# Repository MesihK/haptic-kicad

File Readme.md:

## Motor Controller Device for Zenom Hardware In-the-loop Environment

This device is used for nonliner control of mechanical systems via 
actuators.

Mesih Veysi Kilinc

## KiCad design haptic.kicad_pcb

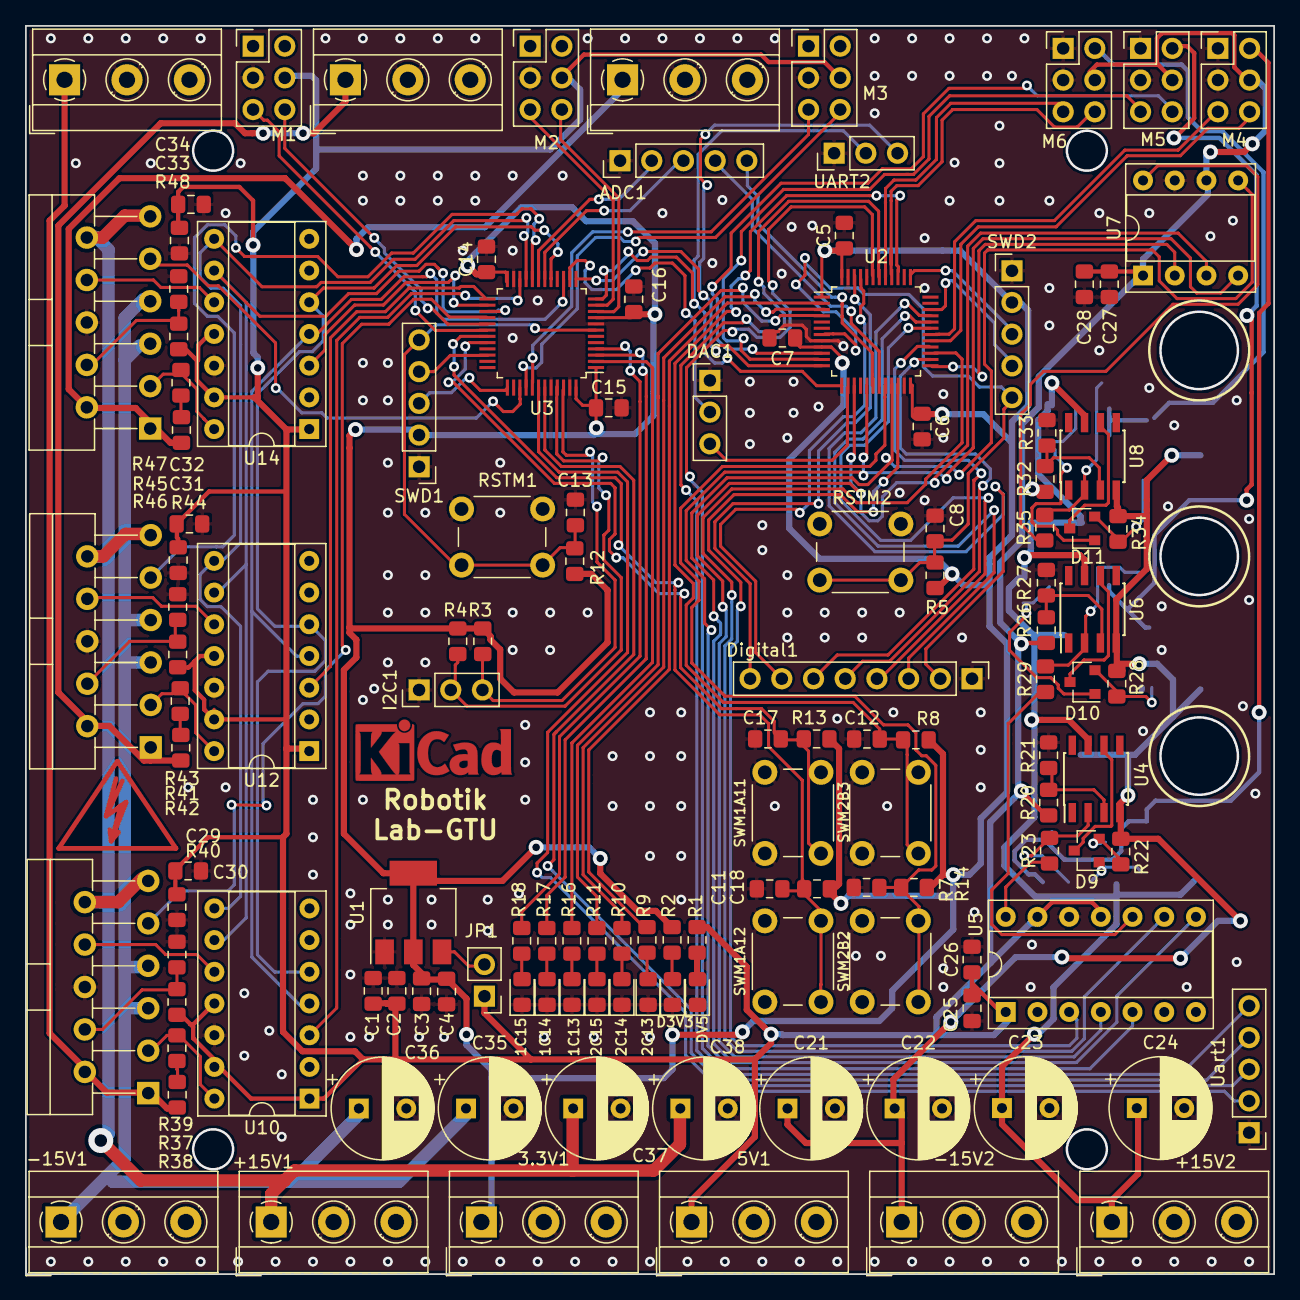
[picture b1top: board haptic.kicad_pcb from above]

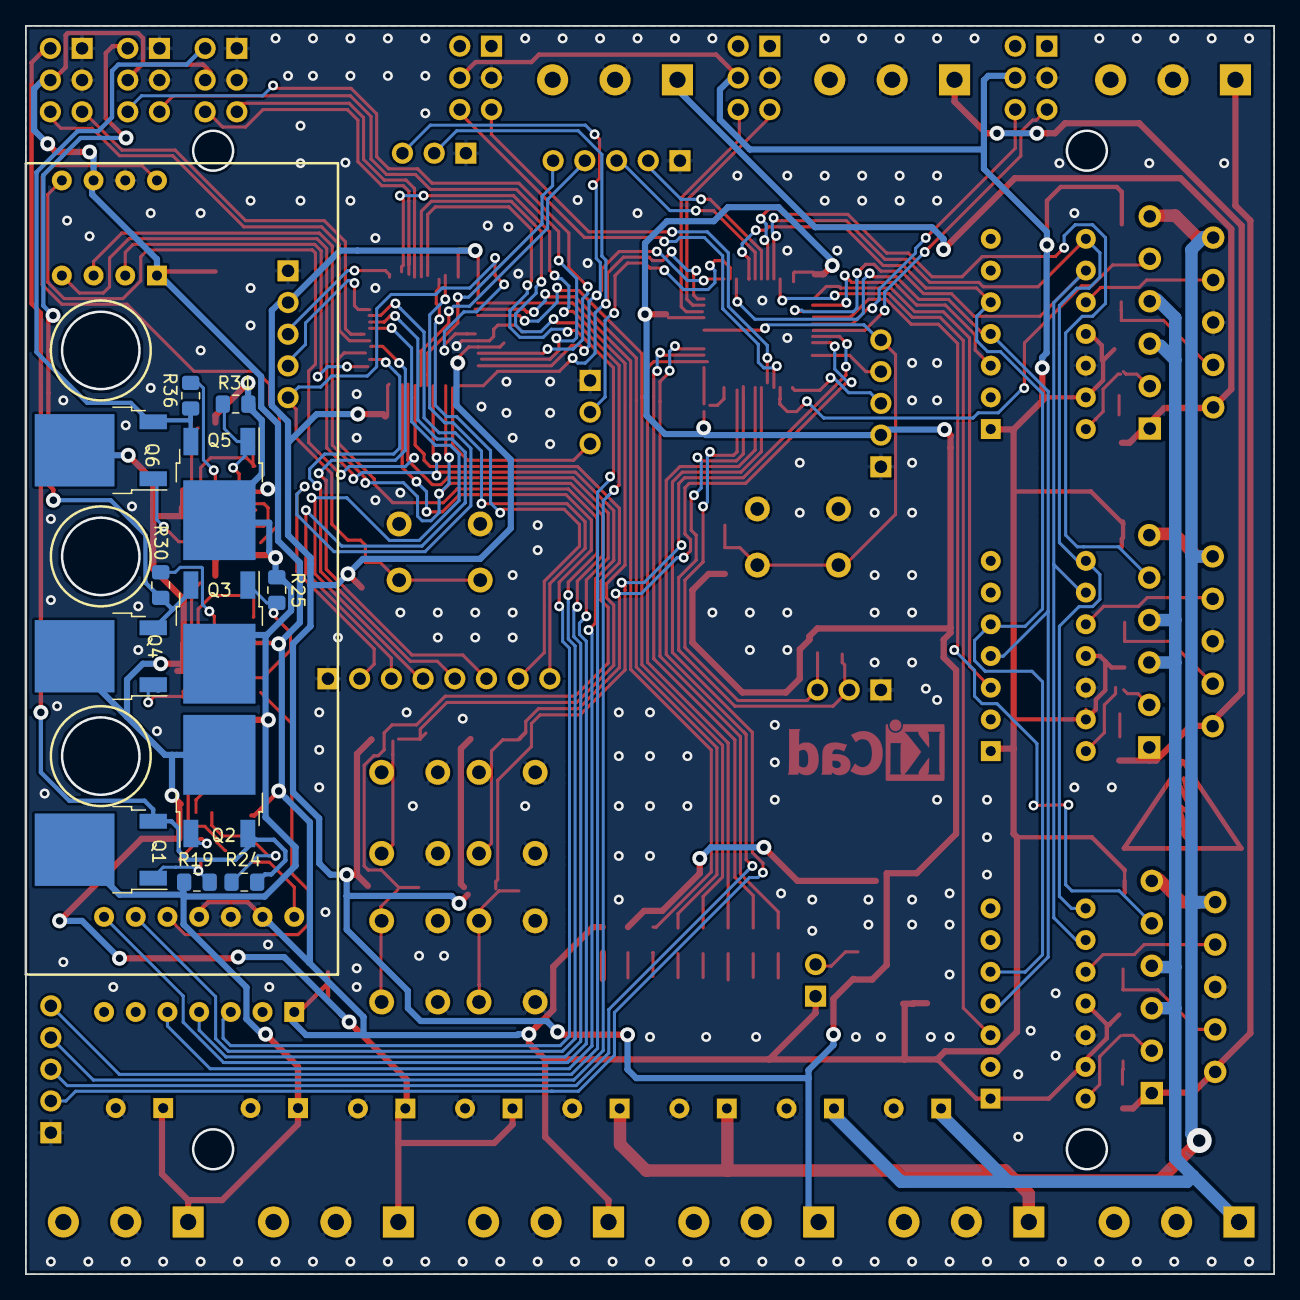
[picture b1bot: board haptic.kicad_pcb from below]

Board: 2 copper layers, 100.0 x 100.0 mm, 141 parts (12 on the bottom side), 117 nets.

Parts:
1C13, 1C14, 1C15, 2C13, 2C14, 2C15: LED; LED_0805_2012Metric_Pad1.15x1.40mm_HandSolder
3.3V1, 5V1: Pow; TerminalBlock_1x03_P5.00mm_Horizontal
+15V1, +15V2: Pow; TerminalBlock_1x03_P5.00mm_Horizontal
-15V1, -15V2: Pow; TerminalBlock_1x03_P5.00mm_Horizontal
ADC1: Analog; PinHeader_1x05_P2.54mm_Vertical
C1, C3, C5, C14, C25, C27, C29, C31, C33: 10u; C_0805_2012Metric_Pad1.15x1.40mm_HandSolder
C2, C4, C6, C7, C8, C11, C12, C13, C15, C16, C17, C18, C26, C28, C30, C32, C34: 100n; C_0805_2012Metric_Pad1.15x1.40mm_HandSolder
C21, C23, C35, C37: 10u; CP_Radial_D8.0mm_P3.80mm
C22, C24, C36, C38: 100n; CP_Radial_D8.0mm_P3.80mm
D3V3: LED; LED_0805_2012Metric_Pad1.15x1.40mm_HandSolder
D9, D10, D11: BAV199; SOT-23
DAC1: DAC; PinHeader_1x03_P2.54mm_Vertical
DV5: LED; LED_0805_2012Metric_Pad1.15x1.40mm_HandSolder
Digital1: Digital2; PinHeader_1x08_P2.54mm_Vertical
I2C1: I2C; PinHeader_1x03_P2.54mm_Vertical
J18, J20, J22: MPow; TerminalBlock_1x03_P5.00mm_Horizontal
JP1: Jumper; PinHeader_1x02_P2.54mm_Vertical
M1, M2, M3, M4, M5, M6: MCon; PinHeader_2x03_P2.54mm_Vertical
Q1, Q3, Q5: MJD31; TO-252-2
Q2, Q4, Q6: MJD32; TO-252-2
R1, R2, R9, R10, R11, R16, R17, R18: 330; R_0805_2012Metric_Pad1.15x1.40mm_HandSolder
R3, R4, R5, R7, R8, R12, R13, R14, R19, R21, R22, R23, R25, R27, R28, R29, R31, R33, R34, R35, R37, R39, R41, R43, R45, R47: 10k; R_0805_2012Metric_Pad1.15x1.40mm_HandSolder
R20, R24, R26, R30, R32, R36: 22k; R_0805_2012Metric_Pad1.15x1.40mm_HandSolder
R38, R42, R46: 100k; R_0805_2012Metric_Pad1.15x1.40mm_HandSolder
R40, R44, R48: 6.8k; R_0805_2012Metric_Pad1.15x1.40mm_HandSolder
RSTM1, RSTM2: Reset; SW_PUSH_6mm
SWD1, SWD2: Debug; PinHeader_1x05_P2.54mm_Vertical
SWM1A11: PB1; SW_PUSH_6mm
SWM1A12: PB2; SW_PUSH_6mm
SWM2B2: PB3; SW_PUSH_6mm
SWM2B3: PB4; SW_PUSH_6mm
U1: AMS1117-3.3; SOT-223-3_TabPin2
U2, U3: STM32F051C8Tx; LQFP-48_7x7mm_P0.5mm
U4, U6, U8: TL081; SOIC-8_3.9x4.9mm_P1.27mm
U5, U10, U12, U14: MCP4922-ESL; DIP-14_W7.62mm_Socket
U7: MCP4921-ESN; DIP-8_W7.62mm_Socket
U9, U11, U13: OPA549; TO-220-11_P3.4x5.08mm_StaggerOdd_Lead4.85mm_Vertical
UART2: DAC; PinHeader_1x03_P2.54mm_Vertical
Uart1: Serial1; PinHeader_1x05_P2.54mm_Vertical

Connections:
+3V3: 3.3V1.1, C3.1, C4.1, C5.1, C6.1, C7.1, C14.1, C15.1, C16.1, R2.1, R3.1, R4.1, R5.1, R7.1, R8.1, R12.1, R13.1, R14.1, SWD1.2, SWD2.2, U1.2, U2.1, U2.9, U2.24, U2.48, U3.1, U3.9, U3.24, U3.48
+5V: 5V1.1, C1.1, C2.1, C25.1, C26.1, C27.1, C28.1, C29.1, C30.1, C31.1, C32.1, C33.1, C34.1, JP1.1, M1.4, M2.4, M3.4, M4.4, M5.4, M6.4, R1.1, R20.1, R26.1, R32.1, R39.1, R43.1, R47.1, U5.1, U5.11, U5.13, U7.1, U7.6, U10.1, U10.11, U10.13, U12.1, U12.11, U12.13, U14.1, U14.11, U14.13
+10V: +15V2.1, C23.1, C24.1, Q1.2, Q3.2, Q5.2, R19.1, R25.1, R31.1, U4.7, U6.7, U8.7
+15V: +15V1.1, C37.1, C38.1, U9.10, U9.11, U11.10, U11.11, U13.10, U13.11
-10V: -15V2.1, C21.1, C22.1, Q2.2, Q4.2, Q6.2, R22.2, R28.2, R34.2, U4.4, U6.4, U8.4
-15V: -15V1.1, C35.1, C36.1, U9.5, U9.7, U11.5, U11.7, U13.5, U13.7
/DAC_SHDN_1: U3.27, U10.9, U12.9, U14.9
/DAC_SHDN_2: U2.27, U5.9
/LDAC_1: U3.21, U10.8, U12.8, U14.8
/LDAC_2: U2.21, U5.8, U7.5
/LowPowerMotorDrive/OP_IN_1: R23.1, U5.14
/LowPowerMotorDrive/OP_IN_2: R29.1, U5.10
/LowPowerMotorDrive/OP_IN_3: R35.1, U7.8
/LowPowerMotorDrive/OP_OUT_1: M4.2, Q1.3, Q2.3, R24.1
/LowPowerMotorDrive/OP_OUT_2: M5.2, Q3.3, Q4.3, R30.1
/LowPowerMotorDrive/OP_OUT_3: M6.2, Q5.3, Q6.3, R36.1
/M1_A11: C17.1, R13.2, SWM1A11.2, U3.32
/M1_A12: C11.1, R7.2, SWM1A12.2, U3.31
/M1_ADC8: ADC1.3, U3.18
/M1_ADC9: ADC1.2, U3.19
/M1_DAC: DAC1.2, U3.14
/M1_DAC_CS1: U3.22, U10.3
/M1_DAC_CS2: U3.25, U12.3
/M1_DAC_CS3: U3.26, U14.3
/M1_I2C_SCL: I2C1.2, R4.2, U3.45
/M1_I2C_SDA: I2C1.3, R3.2, U3.46
/M1_NRST: C13.1, R12.2, RSTM1.2, SWD1.5, U3.7
/M1_SPI_MOSI: U3.17, U10.5, U12.5, U14.5
/M1_SPI_SCK: U3.15, U10.4, U12.4, U14.4
/M1_SWCLK: SWD1.3, U3.37
/M1_SWDIO: SWD1.4, U3.34
/M1_TIM1_CH1: M1.6, U3.29
/M1_TIM1_CH2: M1.5, U3.30
/M1_TIM2_CH1: M2.6, U3.10
/M1_TIM2_CH2: M2.5, U3.11
/M1_TIM3_CH1: M3.6, U3.40
/M1_TIM3_CH2: M3.5, U3.41
/M1_USART1_RX: U3.43, Uart1.3
/M1_USART1_TX: U3.42, Uart1.2
/M1_USART2_RX: U2.12, U3.13, UART2.3
/M1_USART2_TX: U2.13, U3.12, UART2.2
/M2_A10: Digital1.2, U2.33
/M2_A11: Digital1.3, U2.32
/M2_A12: Digital1.4, U2.31
/M2_ADC8: ADC1.5, U2.18
/M2_ADC9: ADC1.4, U2.19
/M2_B2: C18.1, R14.2, SWM2B2.2, U2.20
/M2_B3: C12.1, R8.2, SWM2B3.2, U2.39
/M2_B8: Digital1.7, U2.45
/M2_B9: Digital1.8, U2.46
/M2_B13: Digital1.5, U2.26
/M2_B15: Digital1.6, U2.28
/M2_DAC: DAC1.3, U2.14
/M2_DAC_CS1: U2.22, U5.3
/M2_DAC_CS2: U2.25, U7.2
/M2_NRST: C8.1, R5.2, RSTM2.2, SWD2.5, U2.7
/M2_SPI_MOSI: U2.17, U5.5, U7.4
/M2_SPI_SCK: U2.15, U5.4, U7.3
/M2_SWCLK: SWD2.3, U2.37
/M2_SWDIO: SWD2.4, U2.34
/M2_TIM1_CH1: M4.6, U2.29
/M2_TIM1_CH2: M4.5, U2.30
/M2_TIM2_CH1: M5.6, U2.10
/M2_TIM2_CH2: M5.5, U2.11
/M2_TIM3_CH1: M6.6, U2.40
/M2_TIM3_CH2: M6.5, U2.41
/M2_USART1_RX: U2.43, Uart1.5
/M2_USART1_TX: U2.42, Uart1.4
/MotorDrive/OP_ILM_1: U9.8, U10.10
/MotorDrive/OP_ILM_2: U11.8, U12.10
/MotorDrive/OP_ILM_3: U13.8, U14.10
/MotorDrive/OP_IN_1: R37.1, U9.3, U10.14
/MotorDrive/OP_IN_2: R41.1, U11.3, U12.14
/MotorDrive/OP_IN_3: R45.1, U13.3, U14.14
/OP_ES_1: U3.28, U9.9
/OP_ES_2: U3.20, U11.9
/OP_ES_3: U3.39, U13.9
GND: 1C13.1, 1C14.1, 1C15.1, 2C13.1, 2C14.1, 2C15.1, 3.3V1.2, 5V1.2, +15V1.2, +15V2.2, -15V1.2, -15V2.2, ADC1.1, C1.2, C2.2, C3.2, C4.2, C5.2, C6.2, C7.2, C8.2, C11.2, C12.2, C13.2, C14.2, C15.2, C16.2, C17.2, C18.2, C21.2, C22.2, C23.2, C24.2, C25.2, C26.2, C27.2, C28.2, C29.2, C30.2, C31.2, C32.2, C33.2, C34.2, C35.2, C36.2, C37.2, C38.2, D3V3.1, DAC1.1, DV5.1, Digital1.1, I2C1.1, J18.2, J20.2, J22.2, M1.3, M2.3, M3.3, M4.1, M4.3, M5.1, M5.3, M6.1, M6.3, R21.2, R27.2, R33.2, R40.2, R44.2, R48.2, RSTM1.1, RSTM2.1, SWD1.1, SWD2.1, SWM1A11.1, SWM1A12.1, SWM2B2.1, SWM2B3.1, U1.1, U2.8, U2.23, U2.44, U2.47, U3.8, U3.23, U3.44, U3.47, U5.12, U7.7, U9.6, U10.12, U11.6, U12.12, U13.6, U14.12, UART2.1, Uart1.1
unnamed: 1C13.2, R16.2
unnamed: 1C14.2, R17.2
unnamed: 1C15.2, R18.2
unnamed: 2C13.2, R9.2
unnamed: 2C14.2, R10.2
unnamed: 2C15.2, R11.2
unnamed: D3V3.2, R2.2
unnamed: D9.1, Q1.1, R19.2
unnamed: D9.2, Q2.1, R22.1
unnamed: D9.3, U4.6
unnamed: D10.1, Q3.1, R25.2
unnamed: D10.2, Q4.1, R28.1
unnamed: D10.3, U6.6
unnamed: D11.1, Q5.1, R31.2
unnamed: D11.2, Q6.1, R34.1
unnamed: D11.3, U8.6
unnamed: DV5.2, R1.2
unnamed: J18.1, R38.1, U9.1, U9.2
unnamed: J20.1, R42.1, U11.1, U11.2
unnamed: J22.1, R46.1, U13.1, U13.2
unnamed: JP1.2, U1.3
unnamed: R9.1, U2.2
unnamed: R10.1, U2.3
unnamed: R11.1, U2.4
unnamed: R16.1, U3.2
unnamed: R17.1, U3.3
unnamed: R18.1, U3.4
unnamed: R20.2, R21.1, U4.3
unnamed: R23.2, R24.2, U4.2
unnamed: R26.2, R27.1, U6.3
unnamed: R29.2, R30.2, U6.2
unnamed: R32.2, R33.1, U8.3
unnamed: R35.2, R36.2, U8.2
unnamed: R37.2, R38.2
unnamed: R39.2, R40.1, U9.4
unnamed: R41.2, R42.2
unnamed: R43.2, R44.1, U11.4
unnamed: R45.2, R46.2
unnamed: R47.2, R48.1, U13.4

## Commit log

2019-02-21 pcb v1
2020-01-20 Add readme
